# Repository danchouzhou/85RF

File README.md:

# 85RF
A 2.4G remote control made with ATtiny85

## Fetures
- ATtiny85 compatible with Arduino IDE
- nRF24L01+ / Si24R1 2.4G transceiver
- Zero quiescent current design
- Single CR2032 battery power, select one side to place the battery holder
- Onboard 6-pin AVR-ISP header for developing and re-programming

## Arduino IDE setup
### Board manager
Check out the [installation guide of ATTinyCore](https://github.com/SpenceKonde/ATTinyCore/blob/v2.0.0-devThis-is-the-head-submit-PRs-against-this/Installation.md) by Spence Konde (aka Dr. Azzy)

### Library
This project uses [RF24](https://github.com/nRF24/RF24) by 2bndy5, it's a famous library of nRF24L01. It is possible to install the library directly from the library manager.

## Datasheet
- [Atmel ATtiny25, ATtiny45, ATtiny85 Datasheet](https://ww1.microchip.com/downloads/en/DeviceDoc/Atmel-2586-AVR-8-bit-Microcontroller-ATtiny25-ATtiny45-ATtiny85_Datasheet.pdf)
- [nRF24L01P_PS_v1.0.pdf - Nordic Semiconductor](https://infocenter.nordicsemi.com/pdf/nRF24L01P_PS_v1.0.pdf)
- [Ai-thinker NF-03 Specification](https://docs.ai-thinker.com/_media/nf-03_specification_en.pdf)

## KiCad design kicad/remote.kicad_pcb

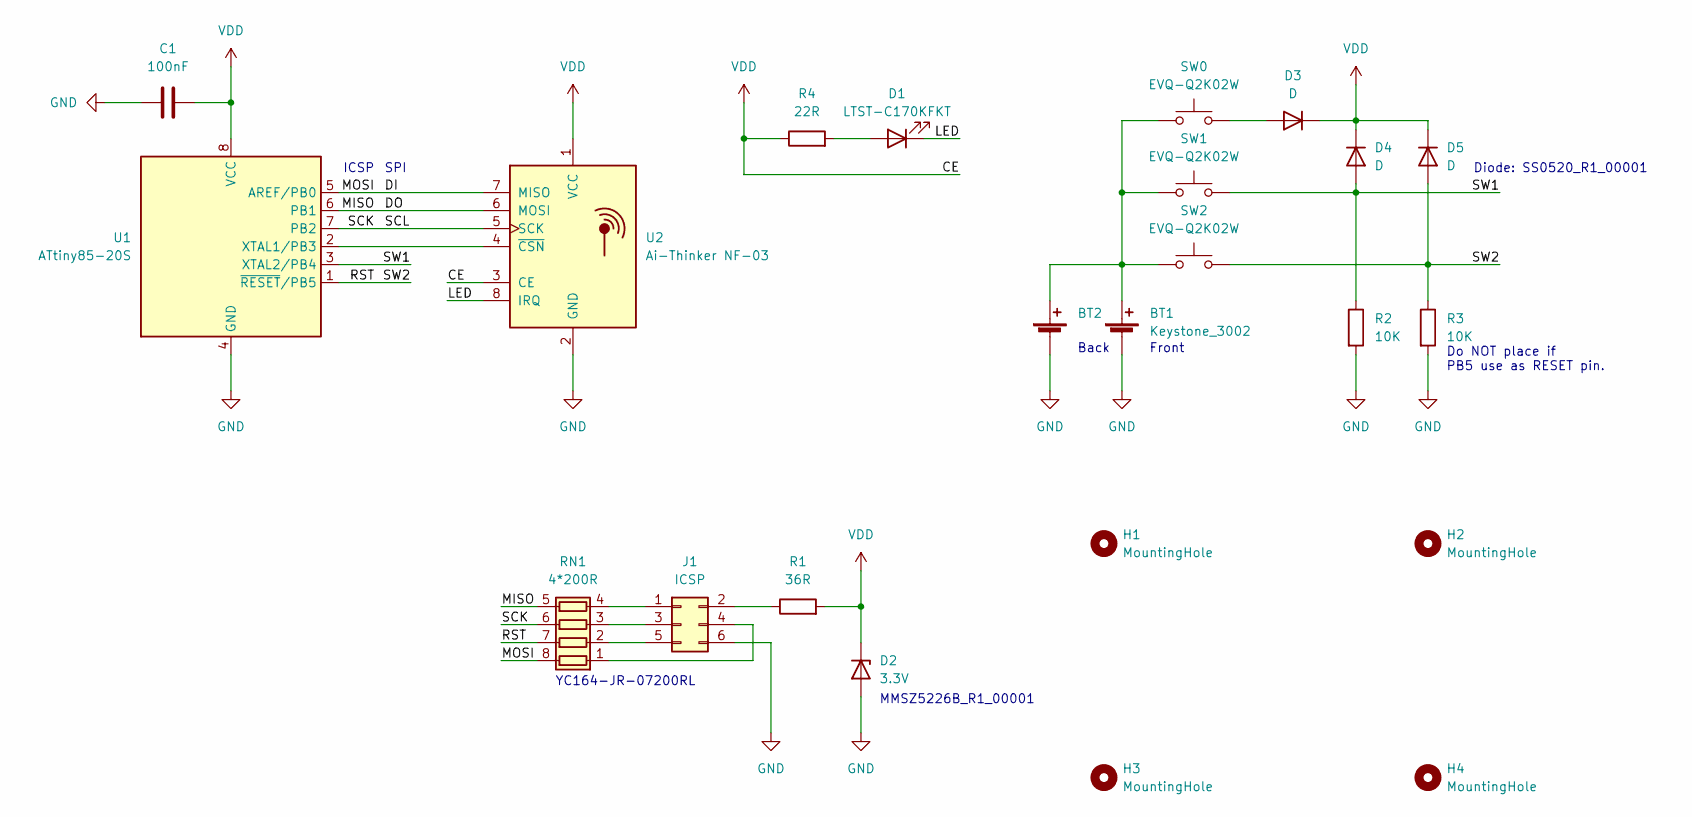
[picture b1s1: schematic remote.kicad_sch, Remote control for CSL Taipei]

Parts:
BT1: Keystone_3002; BatteryHolder_Keystone_3002_1x2032
BT2: BatteryHolder_Keystone_3002_1x2032
C1: 100nF; C_0805_2012Metric
D1: LTST-C170KFKT; LED_0805_2012Metric
D2: 3.3V; D_SOD-123
D3, D4, D5: D; D_SOD-123
H1, H2, H3, H4: MountingHole; MountingHole_2.2mm_M2
J1: ICSP; PinHeader_2x03_P2.54mm_Vertical
R1: 36R; R_0805_2012Metric
R2, R3: 10K; R_0805_2012Metric
R4: 22R; R_0805_2012Metric
RN1: 4*200R; R_Array_Convex_4x0603
SW0, SW1, SW2: EVQ-Q2K02W; SW_SPST_EVQP0
U1: ATtiny85-20S; SOIC-8W_5.3x5.3mm_P1.27mm
U2: Ai-Thinker NF-03; Ai-Thinker-NF-03

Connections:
/DI: RN1.8 (R1.2), U1.5 (AREF/PB0), U2.7 (MISO)
/DO: RN1.5 (R4.2), U1.6 (PB1), U2.6 (MOSI)
/LED: D1.1 (K), U2.8 (IRQ)
/RST: D5.2 (A), R3.1, RN1.7 (R2.2), SW2.2, U1.1 (~RESET/PB5)
/SCK: RN1.6 (R3.2), U1.7 (PB2), U2.5 (SCK)
/SW1: D4.2 (A), R2.1, SW1.2, U1.3 (XTAL2/PB4)
GND: BT1.2 (-), BT2.2 (-), C1.1, D2.2 (A), J1.6, R2.2, R3.2, U1.4 (GND), U2.2 (GND)
unnamed: BT1.1 (+), BT2.1 (+), SW0.1, SW1.1, SW2.1
unnamed: D1.2 (A), R4.2
unnamed: D3.2 (A), SW0.2
unnamed: J1.1, RN1.4 (R4.1)
unnamed: J1.2, R1.1
unnamed: J1.3, RN1.3 (R3.1)
unnamed: J1.4, RN1.1 (R1.1)
unnamed: J1.5, RN1.2 (R2.1)
unnamed: U1.2 (XTAL1/PB3), U2.4 (~CSN)
VDD: C1.2, D2.1 (K), D3.1 (K), D4.1 (K), D5.1 (K), R1.2, R4.1, U1.8 (VCC), U2.1 (VCC), U2.3 (CE)

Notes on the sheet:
Do NOT place if PB5 use as RESET pin.
ICSP
Front
Back
YC164-JR-07200RL
SPI
Diode: SS0520_R1_00001
MMSZ5226B_R1_00001

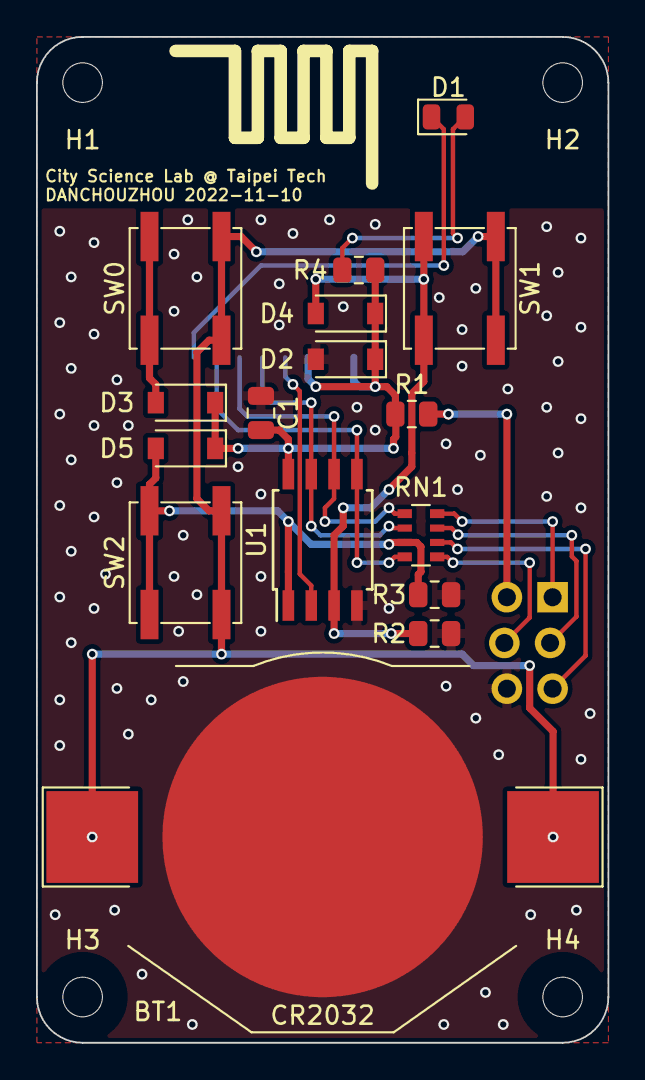
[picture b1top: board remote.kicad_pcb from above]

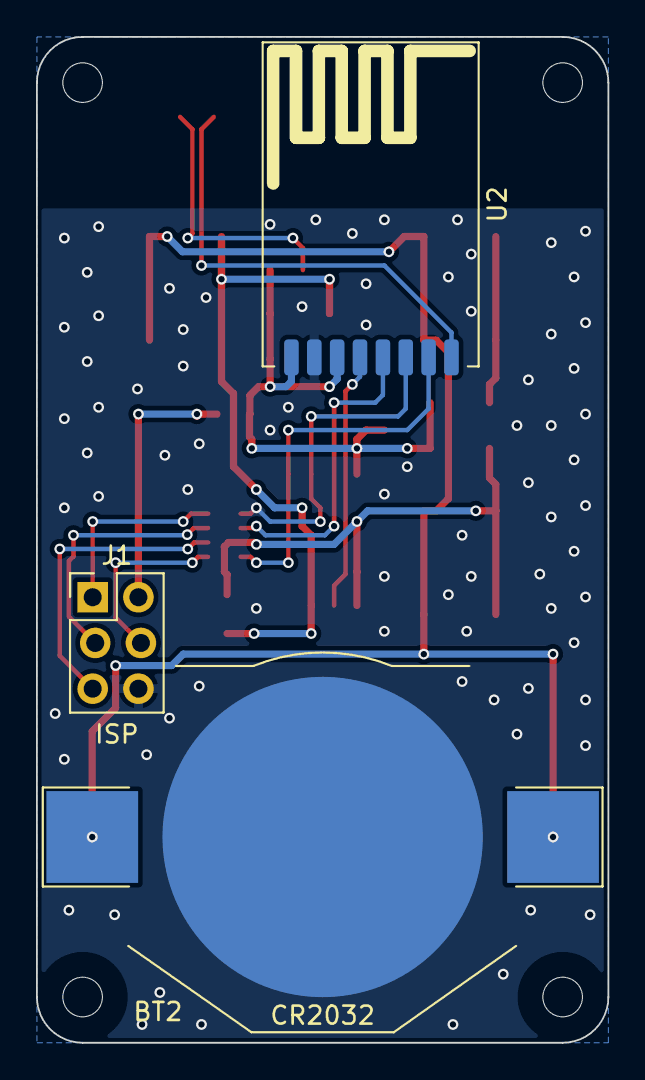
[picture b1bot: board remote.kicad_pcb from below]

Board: 2 copper layers, 31.8 x 55.9 mm, 23 parts (3 on the bottom side), 17 nets.

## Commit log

2022-11-08 Add kicad files
2022-11-10 Update PCB to fit mechanism 1. Change back side battery holder GND pad connection to solid 2. Chnage 'ICSP' to 'ISP' 3. Move ISP header 4. Increase ISP VDD track width 5. Made ISP harder to "Pogo" st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
2022-11-10 Add PCB 3D model

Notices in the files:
kicad/remote.kicad_sch:
Copyright © Danny Chou, all rights reserved.
